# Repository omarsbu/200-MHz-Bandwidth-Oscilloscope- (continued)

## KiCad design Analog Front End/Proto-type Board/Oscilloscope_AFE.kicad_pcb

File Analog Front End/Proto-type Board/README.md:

Stackup:

Top Layer - Signal + Power

Internal Layer 1 - GND

Internal Layer 2 - GND

Bottom Layer - Signal + Power

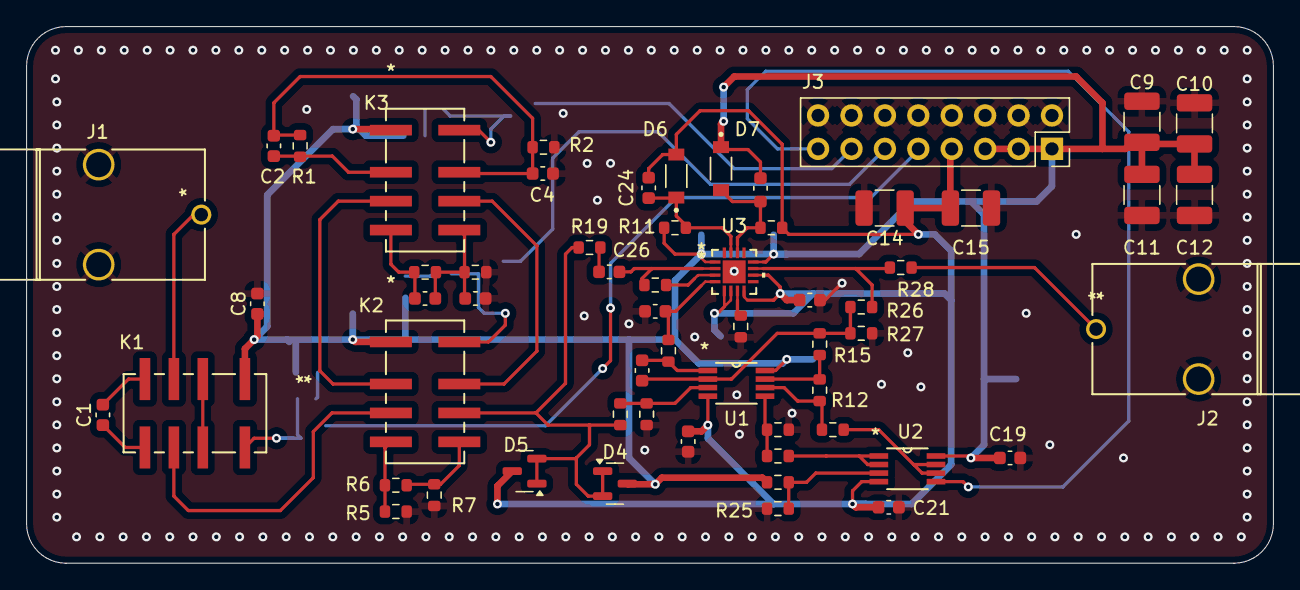
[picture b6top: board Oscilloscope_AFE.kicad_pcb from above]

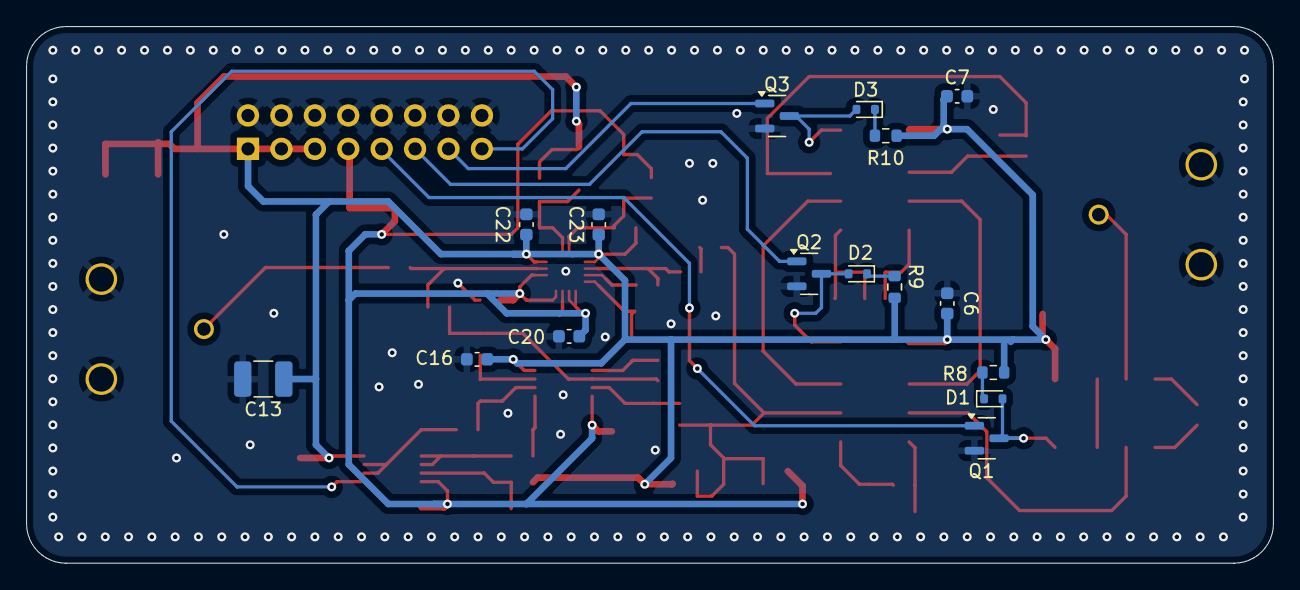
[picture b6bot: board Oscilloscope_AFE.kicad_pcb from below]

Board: 4 copper layers, 94.8 x 40.8 mm, 75 parts (16 on the bottom side), 45 nets.

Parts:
C1, C6, C7, C8, C16, C17, C18, C19, C20, C21, C22, C23: 0.1u; C_0603_1608Metric
C2, C3: 10p; C_0603_1608Metric
C4: 990p; C_0603_1608Metric
C5: 90p; C_0603_1608Metric
C9, C10, C11, C12, C13, C14, C15: 22u; C_1210_3225Metric_Pad1.33x2.70mm_HandSolder
C24, C27: 1u; C_0603_1608Metric
C25: 56p; C_0603_1608Metric
C26: 330p; C_0603_1608Metric
C28: 100p; C_0603_1608Metric
D1, D2, D3: 1N914WT; D_SOD-523
D4, D5: BAT54C; SOT-23
D6, D7: SZMMSZ5233BT1G; DIO_SZMMSZ5233BT1G
J1, J2: BNC; CONN_73100-0105_MOL
J3: Conn_02x08_Odd_Even; PinSocket_2x08_P2.54mm_Vertical
K1, K2, K3: G6J-2FL-Y DC5; RELAY_G6J-2FL-Y DC3_OMR
Q1, Q2, Q3: 2N7002; SOT-23
R1: 990k; R_0603_1608Metric
R2, R24, R25: 10k; R_0603_1608Metric
R3: 900k; R_0603_1608Metric
R4: 100k; R_0603_1608Metric
R5, R7: 75; R_0603_1608Metric
R6: 120; R_0603_1608Metric
R8, R9, R10: 5; R_0603_1608Metric
R11, R20: 1k; R_0603_1608Metric
R12, R16, R17, R18: 500k; R_0603_1608Metric
R13: 833k; R_0603_1608Metric
R14: 167k; R_0603_1608Metric
R15, R26: 80k; R_0603_1608Metric
R19: 30; R_0603_1608Metric
R21: 2k; R_0603_1608Metric
R22: 17.8k; R_0603_1608Metric
R23: 10M; R_0603_1608Metric
R27: 20k; R_0603_1608Metric
R28: 50; R_0603_1608Metric
U1, U2: OPA2140AIDGKR; DGK8
U3: BUF802IRGTR; VQFN16_RGT_TEX

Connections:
+1V_CLAMP: C24.2, D6.1, R11.2, U3.15 (CLH)
+5V: C6.1, C7.1, C8.1, C9.1, C10.1, C11.1, C12.1, C13.1, C16.1, C19.1, C22.1, C23.1, C27.2, D4.3, D7.1, J3.1, J3.3, J3.5, K1.1, K2.1, K3.1, R8.1, R9.1, R10.1, R11.1, R24.1, U1.8, U2.8, U3.1 (VS+), U3.12 (VSO+)
-1V_CLAMP: C27.1, D7.2, R20.1, U3.14 (CLL)
-5V: C14.1, C15.1, C17.1, C18.1, C20.1, C21.1, C24.1, D5.3, D6.2, J3.7, R20.2, U1.4, U2.4, U3.5 (VS-), U3.6 (AUX_BIAS), U3.8 (VS-__1), U3.10 (VSO-)
/Attenuators and Input Coupling/1MΩ Path: K2.2, K3.3
/Attenuators and Input Coupling/10:1 Attenuator: C3.1, C5.1, K3.5, R3.1, R4.1
/Attenuators and Input Coupling/50Ω Path: K2.4, R5.1, R6.2
/Attenuators and Input Coupling/100:1 Attenuator: C2.1, C4.1, K3.7, R1.1, R2.1
/Attenuators and Input Coupling/AC_PATH: C1.1, K1.5
/Attenuators and Input Coupling/ATTEN_OUT: D4.1, D4.2, D5.1, D5.2, K2.6, R13.1, R19.1
/Attenuators and Input Coupling/DC_PATH: K1.2, K1.7
/Attenuators and Input Coupling/IN: J1.1 (In), K1.3
/Attenuators and Input Coupling/RELAY_CTRL_0: J3.9, Q1.1 (G)
/Attenuators and Input Coupling/RELAY_CTRL_1: J3.11, Q2.1 (G)
/Attenuators and Input Coupling/RELAY_CTRL_2: J3.13, Q3.1 (G)
/JFET Buffer/BUFF_OUT: J2.1 (In), R28.2
/JFET Buffer/DC_OFFSET: J3.15, U2.5 (+)
GND: C4.2, C5.2, C6.2, C7.2, C8.2, C9.2, C10.2, C11.2, C12.2, C13.2, C14.2, C15.2, C16.2, C17.2, C18.2, C19.2, C20.2, C21.2, C22.2, C23.2, C28.1, J1.2 (Ext), J1.3, J2.2 (Ext), J2.3, J3.2, J3.4, J3.6, J3.8, J3.10, J3.12, J3.14, J3.16, Q1.2 (S), Q2.2 (S), Q3.2 (S), R2.2, R4.2, R5.2, R7.2, R14.2, R16.2, R22.2, R25.2, R27.2, U3.17 (EXP)
unnamed: C1.2, K1.4
unnamed: C2.2, K3.2, R1.2
unnamed: C3.2, K3.4, R3.2
unnamed: C25.2, R21.1, U1.1
unnamed: C26.1, R19.2
unnamed: D1.2 (A), K1.8, Q1.3 (D)
unnamed: D1.1 (K), R8.2
unnamed: D2.2 (A), K2.8, Q2.3 (D)
unnamed: D2.1 (K), R9.2
unnamed: D3.2 (A), K3.8, Q3.3 (D)
unnamed: D3.1 (K), R10.2
unnamed: K1.6, K2.3
unnamed: K2.5, R6.1, R7.1
unnamed: K2.7, K3.6
unnamed: R12.2, R15.2, U1.7
unnamed: R13.2, R14.1, U1.3 (+)
unnamed: C25.1, R15.1, R26.2, R27.1, U1.2 (-)
unnamed: R16.1, R17.2, U1.5 (+)
unnamed: R12.1, R18.2, U1.6 (-)
unnamed: R24.2, R25.1, U2.3 (+)
unnamed: R17.1, U2.1, U2.2 (-)
unnamed: R18.1, U2.6 (-), U2.7
unnamed: C26.2, R23.1, U3.2 (IN)
unnamed: C28.2, R21.2, U3.4 (IN_AUX)
unnamed: R23.2, U3.3 (IN_BIAS)
unnamed: R26.1, R28.1, U3.11 (OUT)
unnamed: R22.1, U3.7 (R_BIAS)

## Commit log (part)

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2024-05-19 Rename STFT_reconstruction.mlx to STFT_reconstruction.m
2025-01-13 Create misc
2025-01-13 Create miscillaneous
2025-01-13 Rename FPGA/DDS_SIN_COS_GENERATOR.vhd to FPGA/miscellaneous/DDS_SIN_COS_GENERATOR.vhd
2025-01-13 Rename FPGA/DDS_SIN_COS_GENERATOR_TB.vhd to FPGA/miscellaneous/DDS_SIN_COS_GENERATOR_TB.vhd
2025-01-13 Rename FPGA/variable_cutoff_filter.vhd to FPGA/miscellaneous/variable_cutoff_filter.vhd
2025-01-13 Rename FPGA/temp.vhd to FPGA/miscellaneous/temp.vhd
2025-01-13 Rename FPGA/iir_filter.vhd to FPGA/miscellaneous/iir_filter.vhd
2025-01-13 Rename FPGA/fir_filter_tb.vhd to FPGA/miscellaneous/fir_filter_tb.vhd
2025-01-13 Rename FPGA/fir_filter.vhd to FPGA/miscellaneous/fir_filter.vhd
2025-01-13 Rename FPGA/filter_coefficients_decimal.txt to FPGA/miscellaneous/filter_coefficients_decimal.txt
2025-01-13 Rename FPGA/filter_coefficients_binary.txt to FPGA/miscellaneous/filter_coefficients_binary.txt
2025-01-13 Rename FPGA/dds_tb.vhd to FPGA/miscellaneous/dds_tb.vhd
2025-01-13 Rename FPGA/dds_modulator_tb.vhd to FPGA/miscellaneous/dds_modulator_tb.vhd
2025-01-13 Rename FPGA/dds_modulator.vhd to FPGA/miscellaneous/dds_modulator.vhd
2025-01-13 Rename FPGA/dds.vhd to FPGA/miscellaneous/dds.vhd
2025-01-13 Rename FPGA/IIR_DECIMATOR_TB.vhd to FPGA/miscellaneous/IIR_DECIMATOR_TB.vhd
2025-01-13 Rename FPGA/IIR_DECIMATOR.vhd to FPGA/miscellaneous/IIR_DECIMATOR.vhd
2025-01-13 Rename iir_decimator.vhd to MULTISTAGE_IIR_DECIMATOR.vhd
2025-01-13 Rename IIR_FILTER_TB.vhd to MULTISTAGE_IIR_FILTER_TB.vhd
2025-01-13 Rename MULTISTAGE_IIR_FILTER_TB.vhd to MULTISTAGE_IIR_DECIMATOR_TB.vhd
2025-01-14 Rename variable_cutoff_filter_tb.vhd to miscellaneous/variable_cutoff_filter_tb.vhd
2025-01-14 Create tb
2025-01-19 Rename counter.vhd to CIRCULAR_FIFO.vhd
2025-01-19 Rename counter_tb.vhd to CIRCULAR_FIFO_TB.vhd
2025-01-19 Rename vga_controller.vhd to VGA_CONTROLLER.vhd
2025-01-19 Rename vga_controller_tb.vhd to VGA_CONTROLLER_TB.vhd
2025-01-21 Rename Ch14.pdf to Chapter 14: Introduction to Digital Filters .pdf
2025-01-21 Create CIC_compensation_filter_coefficients
2025-01-22 Create CIC_filter_visualization
2025-01-22 Update CIC_filter_visualization
2025-01-24 Rename comp_fir.m to Compensation_FIR_for_CIC_filter.m
2025-01-24 Rename lowpass_filter.coe to comp_FIR_for_CIC.coe
2025-01-24 Rename Compensation_FIR_for_CIC.m to Compensation_FIR_for_CIC.m
2025-01-24 Rename README.md to README.md
2025-01-24 Rename comp_FIR_for_CIC.coe to comp_FIR_for_CIC.coe
2025-01-26 Rename FIR_DECIMATOR.vhd to COMPENSATION_FIR_DECIMATOR.vhd
2025-01-26 Rename COMPENSATION_FIR_DECIMATOR.vhd to FIR_DECIMATOR.vhd
2025-01-26 Create VGA_FONT_ROM
2025-01-26 Rename VGA_FONT_ROM to VGA_FONT_ROM.vhd
2025-07-05 Create VGA_TEXT_GENERATOR_TB
2025-07-05 Rename VGA_TEXT_GENERATOR_TB to VGA_TEXT_GENERATOR_TB.vhd
2025-09-06 Rename FPGA/BINARY_TO_BCD.vhd to FPGA/miscellaneous/BINARY_TO_BCD.vhd
2025-09-06 Rename FPGA/CAPTURE_FIFO.vhd to FPGA/miscellaneous/CAPTURE_FIFO.vhd
2025-09-06 Rename FPGA/CAPTURE_FIFO_TB.vhd to FPGA/miscellaneous/CAPTURE_FIFO_TB.vhd
2025-09-06 Rename FPGA/CIC_FILTER.vhd to FPGA/miscellaneous/CIC_FILTER.vhd
2025-09-06 Rename FPGA/CIC_FILTER_TB.vhd to FPGA/miscellaneous/CIC_FILTER_TB.vhd
2025-09-06 Rename FPGA/CLK_DIVIDER.vhd to FPGA/miscellaneous/CLK_DIVIDER.vhd
2025-09-06 Rename FPGA/DDS_SIN_COS_GENERATOR.vhd to FPGA/miscellaneous/a/DDS_SIN_COS_GENERATOR.vhd
2025-09-06 Rename FPGA/DUAL_PORT_RAM.vhd to FPGA/miscellaneous/DUAL_PORT_RAM.vhd
2025-09-06 Rename FPGA/FIR_DECIMATOR.vhd to FPGA/miscellaneous/FIR_DECIMATOR.vhd
2025-09-06 Rename FPGA/FIR_DECIMATOR_TB.vhd to FPGA/miscellaneous/FIR_DECIMATOR_TB.vhd
2025-09-06 Rename FPGA/MEMORY_CONTROLLER.vhd to FPGA/miscellaneous/MEMORY_CONTROLLER.vhd
2025-09-06 Rename FPGA/MULTISTAGE_IIR_DECIMATOR.vhd to FPGA/miscellaneous/MULTISTAGE_IIR_DECIMATOR.vhd
2025-09-06 Rename FPGA/MULTISTAGE_IIR_DECIMATOR_TB.vhd to FPGA/miscellaneous/MULTISTAGE_IIR_DECIMATOR_TB.vhd
2025-09-06 Rename FPGA/TRIGGER_MODULE.vhd to FPGA/miscellaneous/TRIGGER_MODULE.vhd
2025-09-06 Rename FPGA/TRIGGER_MODULE_TB.vhd to FPGA/miscellaneous/TRIGGER_MODULE_TB.vhd
2025-09-06 Rename FPGA/VGA_CONTROLLER.vhd to FPGA/miscellaneous/VGA_CONTROLLER.vhd
2025-09-06 Rename FPGA/VGA_CONTROLLER_TB.vhd to FPGA/miscellaneous/VGA_CONTROLLER_TB.vhd
2025-09-06 Rename FPGA/VGA_FONT_ROM.vhd to FPGA/miscellaneous/VGA_FONT_ROM.vhd
2025-09-06 Rename FPGA/VGA_GRID_GENERATOR.vhd to FPGA/miscellaneous/VGA_GRID_GENERATOR.vhd
2025-09-06 Rename FPGA/VGA_GRID_GENERATOR_TB.vhd to FPGA/miscellaneous/VGA_GRID_GENERATOR_TB.vhd
2025-09-06 Rename FPGA/VGA_TEXT_GENERATOR.vhd to FPGA/miscellaneous/VGA_TEXT_GENERATOR.vhd
2025-09-06 Rename FPGA/VGA_WAVEFORM_GENERATOR.vhd to FPGA/miscellaneous/VGA_WAVEFORM_GENERATOR.vhd
2025-09-06 Rename FPGA/VGA_TEXT_GENERATOR_TB.vhd to FPGA/miscellaneous/VGA_TEXT_GENERATOR_TB.vhd
2025-09-06 Rename FPGA/VGA_WAVEFORM_GENERATOR_TB.vhd to FPGA/miscellaneous/VGA_WAVEFORM_GENERATOR_TB.vhd
2025-09-20 Rename DATA_CAPTURE_MODULE.vhd to DATA_ACQUISITION_MODULE.vhd
2025-09-20 Rename MEMORY_CONTROLLER.vhd to VGA_MEMORY_CONTROLLER.vhd
2025-09-20 Rename VGA_CONTROLLER.vhd to VGA_MUXvhd
2025-09-20 Rename VGA_MUXvhd to VGA_MUX.vhd
2025-09-20 Rename VGA_SCOPE_TOP_LEVEL.vhd to TOP_LEVEL.vhd
2025-09-21 Rename an-1026-High_Speed_Differential_ADC_Driver_Design_Considerations.pdf to Analog Front End/an-1026-High_Speed_Differential_ADC_Driver_Design_Considerations.pdf
2025-09-21 Rename Analog Front End/an-1026-High_Speed_Differential_ADC_Driver_Design_Considerations.pdf to Analog Front End/AFE Research/an-1026-High_Speed_Differential_ADC_Driver_Design_Considerations.pdf
